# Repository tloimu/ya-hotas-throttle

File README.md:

# Yet-Another HOTAS Throttle (YA-HOTAS-THROTTLE)

This 3D printable HOTAS throttle game controller. It connects as a standard USB joystick to Windows without needing to install any software.

It has:

 - 3 axis (throttle, vertical, horizontal) with center detents an all
 - 7 buttons
 - hat switch with 8 directions and press button
 - lock/program button
 - RGB LED indicating state: throttle center (green), locked (red), program (blue)
 - high quality mechanical and electro-mechanical components
 - very smooth and easy throttle action with no stiction
 - adjustable throttle handle angle (twist) for better ergonomics at different table positioning
 - customizable throttle axis detents
 - host additional USB serial connectivity for debugging and programming

**Complete Design Explosion View**

**A photo of an actual build (don't mind the colors - this is a fully working prototype build)**

**And when fully opened**

# Design

The design is based on these guidelines:

 - all buttons and knobs must be reachable without moving the palm on the hand
 - smooth and precise throttle operation
 - angled design for better ergonomics to miminize stress of the wrist and arm
 - parameterized design for tweaking ergonomics and control placement
 - allow some key build-time mechanical tuning options in case printing precision is not perfect
 - modularity for better flexibility and extensibility

The design is mostly parametrisized so that you can customize it to fit e.g. a bit larger hands better or different angles. This one is optimized for my smaller hands (e.g. Saitek X45 throttle was too big for my hands) so that I can reach all knobs and switches without moving my palm.

The microcontroller was placed in the handle section to minimize the amount of wires needed to be moved as the throttle is used. This and the cable management was design to allow completely smooth operation of the throttle so that the cables won't hinder or move the throttle at any position.

# Build

All 3D printable parts are designed using OpenSCAD and I printed them using my Prusa MK3S running the default .40mm nozzle. Most parts can be printed with 0.30mm layer height but some require 0.20mm layers to get proper results.

Before printing the thumb-side, add supports to the couple of screw locations like below.

Some parts require or benefit from post-print processing:

 - drill the five button holes with e.g. 8.5mm drill to make the button hole walls smooth and the buttons will work smoother - you might also need to gently file the outsides of the buttons too if there is stuff left from printing to get them fit and move well
 - some screw holes may benefit from drilling for easier fit (2.5mm for inner screwholes and 3mm for screwholes on circuitboards)
 - throttle center detent hole could be drilled bigger for stronger detent or cone shaped with a bit larger drill head for smoother detent exit/entry

Below is an illustration of all printable parts.

Connect the wires like this to match the code:

| Arduino Pin | Circuit  |
| ----        | ----     |
| 8           | Row 1    |
| 6           | Row 2    |
| 0           | Row 3    |
| 10          | Col 1    |
| 4           | Col 2    |
| 9           | Col 3    |
| 1           | Col 4    |
| 12          | Col 5    |
| 5           | Col 6    |
| 7           | Col 7    |
| 11          | Col 8    |
| 21          | Rx       |
| 22          | Ry       |
| 20          | Throttle |
| 19          | Slider   |

The circuit board could look like the below if you use a generic 2.54mm raster board with single sided copper stripes.

Below are some photos of the assembly

outside of the handle

and how to fit everything inside the handle

The cable management is important to make the throttle handle move smoothly and not move on its own at any position due wires pushing it.

## Firmware

Directory **firmware** contains the code for Arduino. I has been tested with Arduino 1.8.9 on Teensy LC with USB Type **Serial + Keyboard + Mouse + Joystick**. You also need to have/install **Bounce2** and **FastLED** libraries. Prebuilt hex-file for Teensy LC is also located in the directory.

## Other Build Notes

Lighly lube the two metal rails, just like you would do for your 3D printer rails.

Ligtly lube the ball spring plunger with silicone based (or other plastic friently lube) for smoother throttle movement and less noise.

The right side of the case top that has the center detent - to get smoother and less noisy throttle movement:

 - apply little silicone lube spray to where the ball spring plunger meets the plastic
 - 3D print it so that the last layer is printed in the same direction as the ball moves! E.g. in Prusa slicer, I rotated this part 45 degrees before printing - see the pic below

The X/Y potentiometers' metal shafts I got required good lubing (e.g. CRC Elektro or teflon spray). They were quite stiff to turn, but lubing them made a big difference. I didn't have this sort of issue with other pots I had, but since I wanted ones with a center detent built-in, had to go with these.

# Parts List

On top of the 3D printable components, you need

 - 2 x linear motion rods 8mm x 168mm (get one longer and cut in two)
 - 2 x linear bearings 8x15x45 (e.g. LM8LUU)
 - 1 x Teensy LC (or another Arduino board with enough pins)
 - 2 x 10kohm LIN pot (e.g. BI Technologies/TT Electronics P160 with center detent, 15mm shaft - P160KN-1QC15B10K)
 - 1 x 100mm travel 10kohm LIN slide pot (BI Technologies/TT Electronics PS100 B 10K 0E)
 - 1 x multidirectional switch 8 dir + center press (Alps RKJXL100401V)
 - 7 x switches (a tact switch with pins fitting the circuit board listed)
 - 1 x slide switch (any generic model you can fit the case)
 - some generic circuit board (0.1" / 2.54mm pin pitch)
 - N x screws (2.5mm and 3mm) for plastic - for case cover, handle thumb section and internal parts
 - 2 x screws 3mm for attaching the rods from one of their ends to the case
 - 2 x screws 2mm for attaching the slide potentiometer
 - 6 x zip ties for attaching the bearings and do cable management, small ones will do
 - wires
 - 1 x RGB LED (WS2812 compatible)
 - 1 x 9.5mm steel ball
 - 1 x steel spring of e.g. 4.5x22mm (one from a regular ball point pen will work well)

The Teensy LC can quite easily be replaced with any Arduino compatible device with USB connectivity and enough pins. With more coding effort any USB capable micro controller that fits the case could also do.

The RGB LED and slide switch (lock/program) are fully optional. The multi-directional hat switch can also easily be left out or replaced with a simpler 4-directional hat switch.

The steel ball and spring are used to make the center detent for the throttle. Different size ball and spring can be used by modifying the printed *BallSpringPlunger* parameters in the OpenSCAD files.

## Lock/Program

I had two options of the Lock-button. One is a slider switch (currently implemented) and another is to use a simple button switch. Either way, once Lock-mode is on, the throttle axis value is locked to its current value. This is to prevent in-game accidents while you're e.g. AFK and your cat jumps on the throttle.

For simple buttons, the following logic could be made. Press and hold Lock-button for a while and all axis will lock onto their current position. Unlock by pressing Lock button once. Double-click Lock-button to switch between secondary mode that redefines all buttons, hat and axis.

# Discussions and Considerations

## Pots vs Hall effect vs rotation encodes

I did consider using hall sensors or even rotational encoders with belt/pulley system, but eventually found them overly complex to assemble over using simple linear slide potentiometer. We're building these by ourselves and making it all too complex only makes less people (including me) actually build it successfully in quality.

The ones I used here (TT Electronics' PS100) are very smooth, accurate enough and are rated for 100000 cycles while costing only 4-5 euros a piece. So, if they still wear out at some point, just replace it with a new one. It's *your* own build anyway and not something you sell in millions while staying clear of warranty claims.

Many rotary systems might also require manual calibration every time the machine is restarted as the absolute position is not necessarily known. I've seen some hall sensor joysticks requiring that and I found it an undesired feature.

I also considered using some form of lever system (like is done e.g. in Thrustmaster's throttle unit) and transfer the linear motion into a rotational potentiometer. But they easily come with some mechanical "play". Also, some inherent non-linearity of such construct would have to be compensated in the code.

## Throttle Handle Twist or Not

The current design allows either fixing the handle in place with a screw or leave the screw out and allow rotating the handle to a location that suits your current sitting position. The fitting of the throttle shaft to the handle is quite stiff on purpose.

It would be relatively easy to add an actual axis to the twist of the handle. Some throttles have a rocker on the front for this. However, I didn't add that here as rudder pedals or joystick with a twisting handle works better. This throttle is *very* smooth and light to operate so asserting any other forces with the same hand would likely interfere with the throttle.

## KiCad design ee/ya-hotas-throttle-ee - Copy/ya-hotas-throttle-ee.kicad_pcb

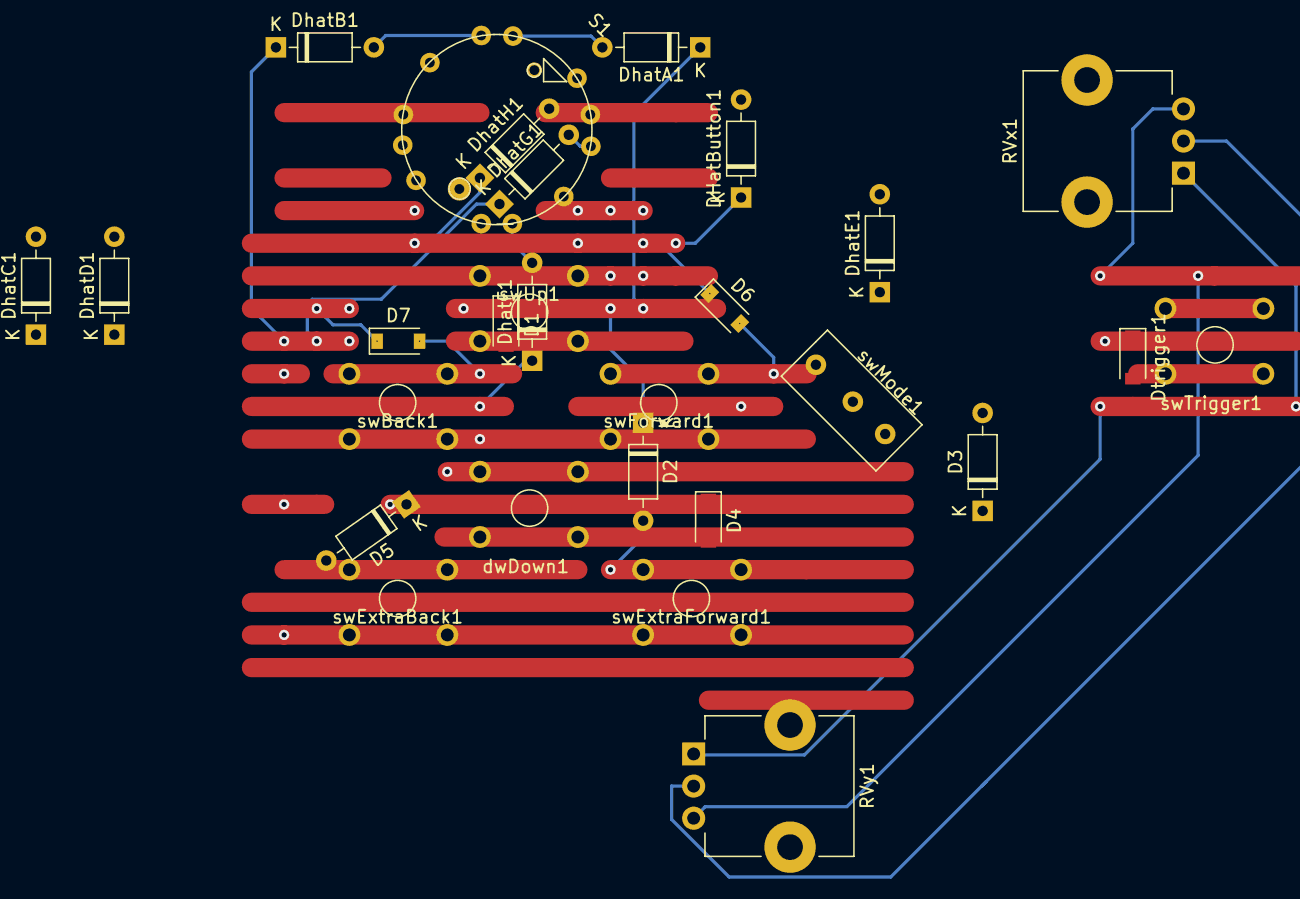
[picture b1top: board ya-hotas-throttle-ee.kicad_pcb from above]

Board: 4 copper layers, 28 parts (0 on the bottom side), 27 nets.

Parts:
D1, D4, D6, D7: 1N4148W; D_SOD-123
D2, D3, D5: 1N4148W; D_DO-35_SOD27_P7.62mm_Horizontal
DHatButton1: 1N4148W; D_DO-35_SOD27_P7.62mm_Horizontal
DhatA1: 1N4148W; D_DO-35_SOD27_P7.62mm_Horizontal
DhatB1: 1N4148W; D_DO-35_SOD27_P7.62mm_Horizontal
DhatC1: 1N4148W; D_DO-35_SOD27_P7.62mm_Horizontal
DhatD1: 1N4148W; D_DO-35_SOD27_P7.62mm_Horizontal
DhatE1: 1N4148W; D_DO-35_SOD27_P7.62mm_Horizontal
DhatF1: 1N4148W; D_DO-35_SOD27_P7.62mm_Horizontal
DhatG1: 1N4148W; D_DO-35_SOD27_P7.62mm_Horizontal
DhatH1: 1N4148W; D_DO-35_SOD27_P7.62mm_Horizontal
Dtrigger1: 1N4148W; D_SOD-123
RVx1: R_POT_Small; Potentiometer_TT_P0915N
RVy1: R_POT_Small; Potentiometer_TT_P0915N
S1: Hat8+press; AlpsRKJXL100401V
dwDown1: SW_MEC_5E; Switch_Tact
swBack1: SW_MEC_5E; Switch_Tact
swExtraBack1: SW_MEC_5E; Switch_Tact
swExtraForward1: SW_MEC_5E; Switch_Tact
swForward1: SW_MEC_5E; Switch_Tact
swMode1: SW_DPDT_x2; Switch_slide_2
swTrigger1: SW_MEC_5E; Switch_Tact
swUp1: SW_MEC_5E; Switch_Tact

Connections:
3.3V: RVx1.1, RVy1.1
GND: RVx1.3, RVy1.3
unnamed: D1.2, swUp1.1
unnamed: D2.2, swExtraForward1.1
unnamed: D3.2, swMode1.3
unnamed: D4.2, dwDown1.1
unnamed: D5.2, swExtraBack1.1
unnamed: D6.2, swForward1.1
unnamed: D7.2, swBack1.1
unnamed: DHatButton1.2, S1.1
unnamed: DhatA1.2, S1.A
unnamed: DhatB1.2, S1.B
unnamed: DhatC1.2, S1.C
unnamed: DhatD1.2, S1.D
unnamed: DhatE1.2, S1.E
unnamed: DhatF1.2, S1.F
unnamed: DhatG1.2, S1.G
unnamed: DhatH1.2, S1.H
unnamed: Dtrigger1.2, swTrigger1.1
col1: D1.1, D2.1, D7.1, DhatA1.1
col2: D4.1, D5.1, DhatC1.1, DhatE1.1
col3: DhatD1.1, DhatF1.1
col4: DhatB1.1, DhatG1.1, Dtrigger1.1
col5: D6.1, DHatButton1.1, DhatH1.1
row1: S1.C1, swUp1.4
row2: S1.2, swExtraBack1.4, swExtraForward1.4
row4: dwDown1.4, swBack1.4, swForward1.4, swTrigger1.4

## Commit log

2021-04-06 Added printed parts preview. Minor updates and clarifications
2021-04-06 Minor updates
2021-04-12 Renamed. Minor updates.
2021-05-10 Printable case, lower profile and improved base and case. 3d code reorg and improved parametrization
2021-05-10 Printed parts stl updated
2021-05-10 Added hat switch knob into preview pic
2021-05-11 Fixed linear slider pot model name
2021-05-15 Minor updates - moved to-do list to Git project tasks
2021-05-27 Started proto 3 handle improvements: two more buttons, firmer assembly, better button module and hat assembly
2021-10-13 Use keyboard matrix, put hat switch to same board as other thumb plate switches, fixes to instructions, add circuit board design and part list
2021-10-13 Updated thumb side circuit board design
2022-02-05 Updated handle pics of v3 implementation
2022-02-05 Prototype v3 (#3)
    * Use keyboard matrix, put hat switch to same board as other thumb plate switches, fixes to instructions, add circuit board design and part list
    * Updated thumb side circuit board design
    * Updated handle pics of v3 implementation
2022-04-24 Redesigned the case and the "guts" of the throttle axis to have more modular, expanable, easier to assemble and lower profile design
2022-04-24 Minor rearrangements
2022-04-24 Fixed full view handle pos and separation
2022-04-24 Minor tweak to full view
2022-06-01 Completely revamped throttle detent system. New cover case with additional button places. Fixed firmware to work better also with no detents set. Improved rendering performance and other smaller fixe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
